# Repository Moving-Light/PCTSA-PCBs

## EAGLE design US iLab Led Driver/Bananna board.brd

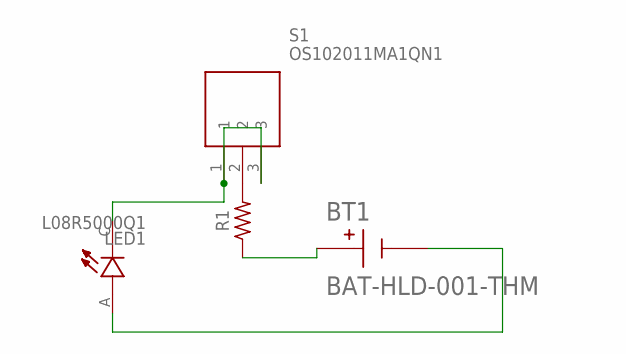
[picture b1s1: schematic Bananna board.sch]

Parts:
BT1: BAT-HLD-001-THM; BAT_BAT-HLD-001-THM
LED1: L08R5000Q1; LEDRD254W57D500H1070
R1: R-US_0207/12; 0207/12
S1: OS102011MA1QN1

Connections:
unnamed: R1.2, S1.2
unnamed: LED1.C, S1.1, S1.3
unnamed: BT1.N, LED1.A
unnamed: BT1.P1, BT1.P2, BT1.P3, BT1.P4, R1.1

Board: 2 copper layers, 4 parts (0 on the bottom side), 4 nets, no tracks yet.

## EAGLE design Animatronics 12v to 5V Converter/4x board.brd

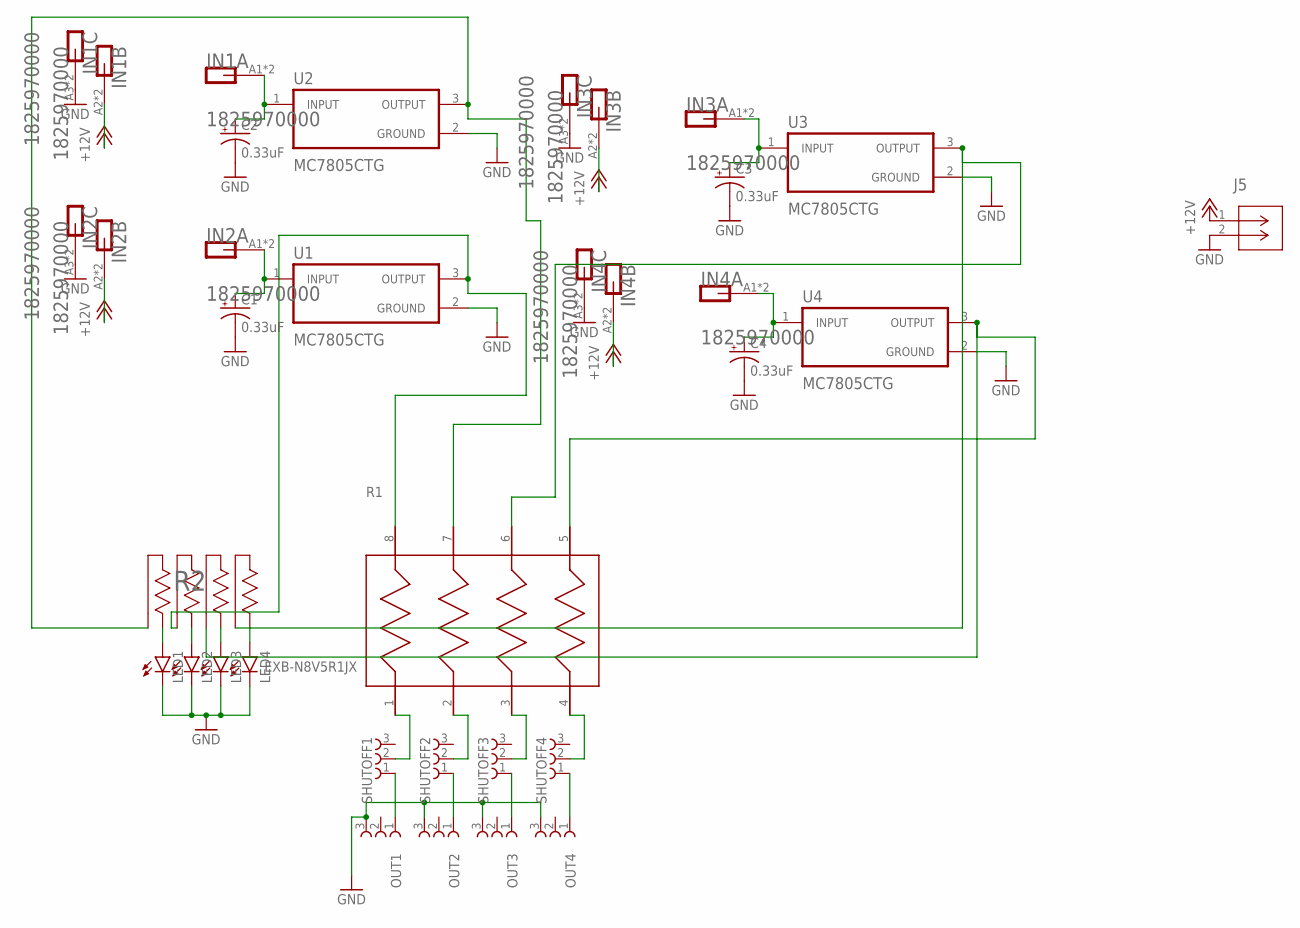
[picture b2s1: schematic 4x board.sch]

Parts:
C1, C2, C3, C4: 0.33uF; E2,5-5
IN1, IN2, IN3, IN4: WEIDMUELLER_1825970000WEIDMUELLER_1825970000_0_0; WEIDMUELLER_1825970000_0
J5: 2606-3102/020-000; CONN3_2606-3102/020-000_WAG
LED1, LED2, LED3, LED4: LED3MM
OUT1, OUT2, OUT3, OUT4: 61300311121
R1: EXB-N8V5R1JX; RESCAV50P200X100X55-8N
R2: 4608X-102-151LF; BO_4608X
SHUTOFF1, SHUTOFF2, SHUTOFF3, SHUTOFF4: 61300311121
U1, U2, U3, U4: MC7805CTG; TO254P1066X482X2286-3

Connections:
+12V: IN1.A2, IN1.A2-2 (A2), IN2.A2, IN2.A2-2 (A2), IN3.A2, IN3.A2-2 (A2), IN4.A2, IN4.A2-2 (A2), J5.1
GND: C1.-, C2.-, C3.-, C4.-, IN1.A3, IN1.A3-2 (A3), IN2.A3, IN2.A3-2 (A3), IN3.A3, IN3.A3-2 (A3), IN4.A3, IN4.A3-2 (A3), J5.2, LED1.K (C), LED2.K (C), LED3.K (C), LED4.K (C), OUT1.3, OUT2.3, OUT3.3, OUT4.3, U1.2 (GROUND), U2.2 (GROUND), U3.2 (GROUND), U4.2 (GROUND)
unnamed: R1.8, R2.3, U1.3 (OUTPUT)
unnamed: C1.+, IN2.A1, IN2.A1-2 (A1), U1.1 (INPUT)
unnamed: R1.1, SHUTOFF1.2
unnamed: R1.7, R2.1, U2.3 (OUTPUT)
unnamed: R1.6, R2.7, U3.3 (OUTPUT)
unnamed: C3.+, IN3.A1, IN3.A1-2 (A1), U3.1 (INPUT)
unnamed: R1.2, SHUTOFF2.2
unnamed: C4.+, IN4.A1, IN4.A1-2 (A1), U4.1 (INPUT)
unnamed: R1.3, SHUTOFF3.2
unnamed: R1.4, SHUTOFF4.2
unnamed: R1.5, R2.5, U4.3 (OUTPUT)
unnamed: OUT1.1, SHUTOFF1.1
unnamed: OUT2.1, SHUTOFF2.1
unnamed: OUT3.1, SHUTOFF3.1
unnamed: OUT4.1, SHUTOFF4.1
unnamed: LED1.A, R2.2
unnamed: LED2.A, R2.4
unnamed: LED3.A, R2.6
unnamed: LED4.A, R2.8
unnamed: C2.+, IN1.A1, IN1.A1-2 (A1), U2.1 (INPUT)

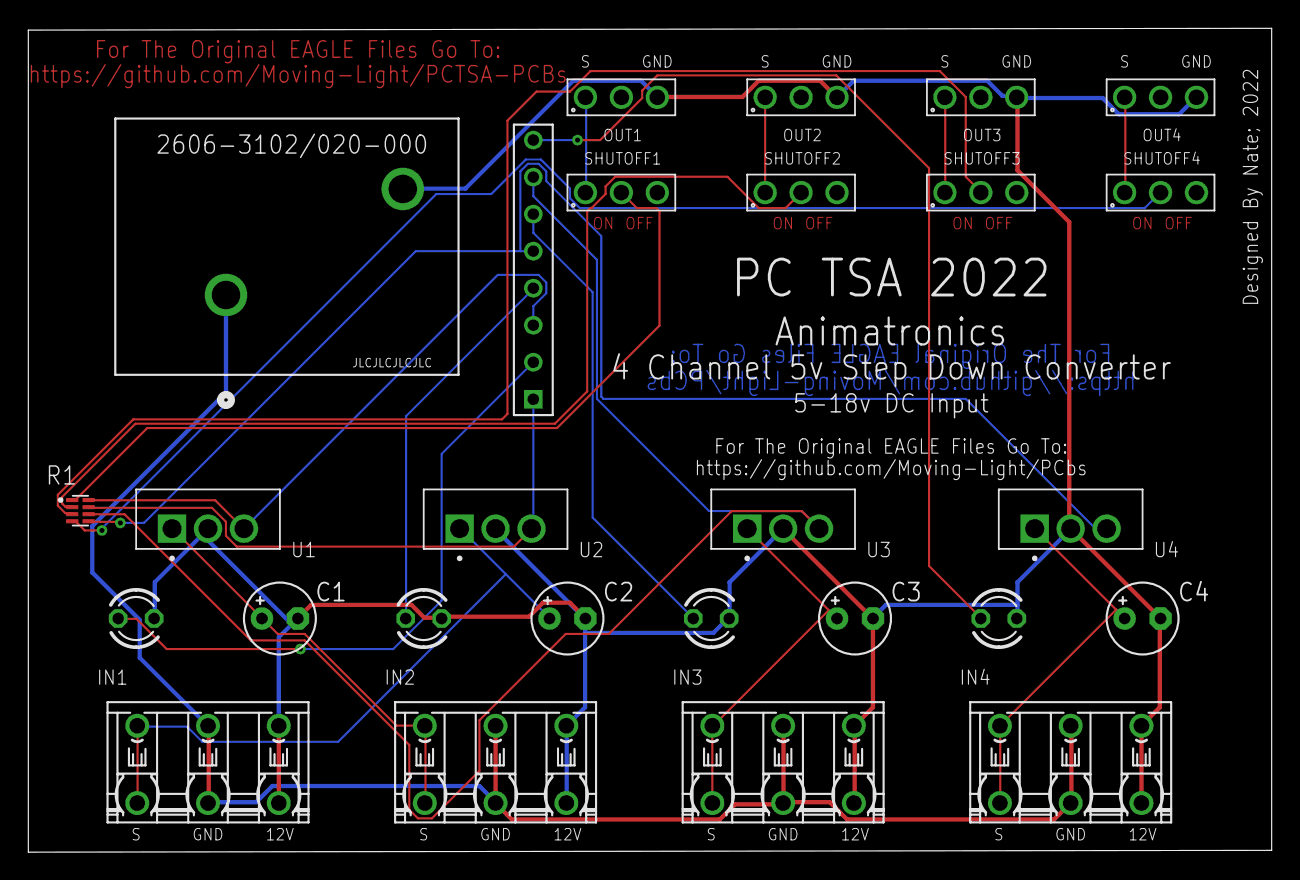
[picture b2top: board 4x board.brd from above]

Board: 2 copper layers, 87.9 x 58.2 mm, 27 parts (0 on the bottom side), 22 nets.

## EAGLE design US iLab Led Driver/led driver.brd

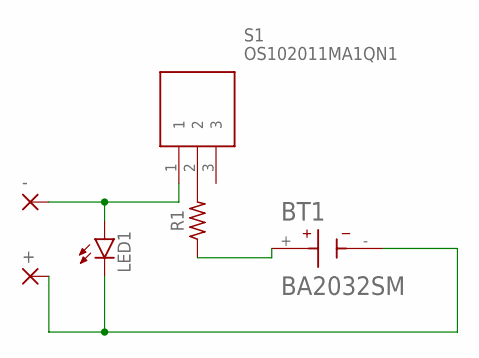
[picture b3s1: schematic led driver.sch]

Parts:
+: 2,54/1,1
-: 2,54/1,1
BT1: BA2032SM; BAT_BA2032SM
LED1: LED5MM
R1: R-US_AXIAL-11.7MM-PITCH; RESAD1176W63L850D250B
S1: OS102011MA1QN1

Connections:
unnamed: R1.2, S1.2
unnamed: -.1, LED1.A, S1.1
unnamed: +.1, BT1.-, LED1.K (C)
unnamed: BT1.+, R1.1

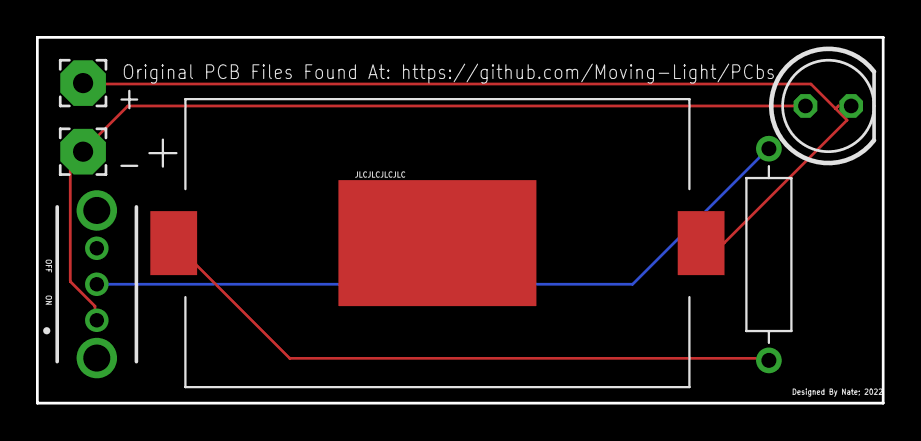
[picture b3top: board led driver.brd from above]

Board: 2 copper layers, 47.0 x 20.3 mm, 6 parts (0 on the bottom side), 4 nets.

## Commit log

2022-01-03 Add .gitignore
2022-01-03 Add TSA Animatronics 12v to 5v Converter
2022-01-03 Added required libraries for parts
2022-01-04 Add lib
2022-01-04 Added Resistor Holes
    Resistor Size:
    Diameter = 2.3mm
    Length = 6mm
2022-01-04 Finished PCB
2022-02-04 Create license
2023-05-09 2023 Update

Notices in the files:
parts and their libraries:
COPYRIGHT: Copyright (C) 2021 Ultra Librarian. All rights reserved.
